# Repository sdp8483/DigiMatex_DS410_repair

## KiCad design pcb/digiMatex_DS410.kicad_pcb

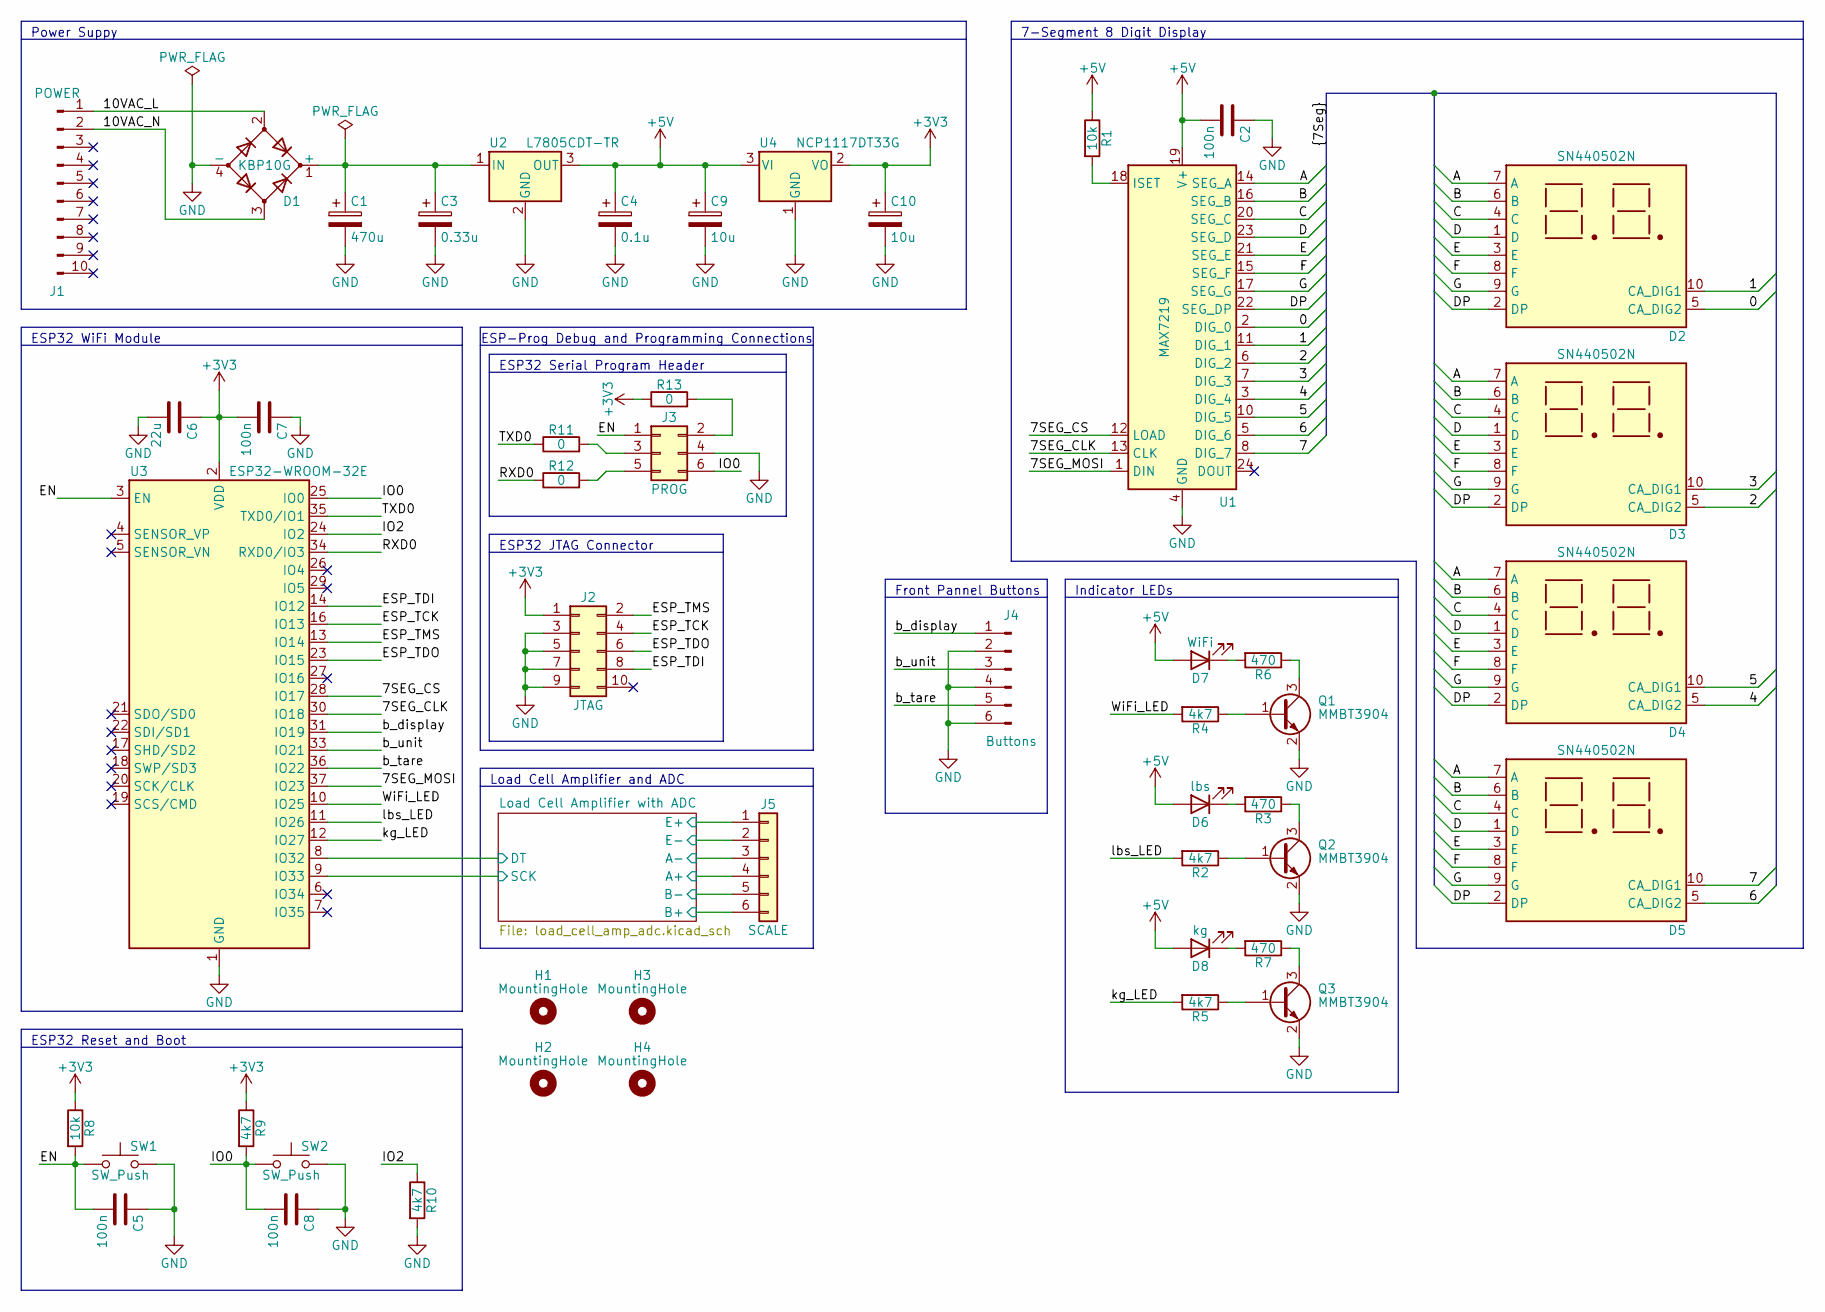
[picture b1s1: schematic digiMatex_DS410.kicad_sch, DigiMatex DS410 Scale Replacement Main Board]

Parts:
C1: 470u; CP_Radial_D10.0mm_P5.00mm
C2, C5, C7, C8: 100n; C_0603_1608Metric
C3: 0.33u; CP_Radial_D6.3mm_P2.50mm
C4: 0.1u; CP_Radial_D6.3mm_P2.50mm
C6: 22u; C_1206_3216Metric
C9, C10: 10u; CP_Radial_D6.3mm_P2.50mm
D1: KBP10G; Diode_Bridge_Vishay_KBPM
D2, D3, D4, D5: SN440502N
D6: lbs; LED_D5.0mm
D7: WiFi; LED_D5.0mm
D8: kg; LED_D5.0mm
H1, H2, H3, H4: MountingHole; MountingHole_4mm_Pad
J1: POWER; Molex_KK-254_AE-6410-10A_1x10_P2.54mm_Vertical
J2: JTAG; PinHeader_2x05_P2.54mm_Vertical
J3: PROG; PinHeader_2x03_P2.54mm_Vertical
J4: Buttons; Molex_KK-254_AE-6410-06A_1x06_P2.54mm_Vertical
J5: SCALE; TerminalBlock_Phoenix_MKDS-1,5-6_1x06_P5.00mm_Horizontal
Q1, Q2, Q3: MMBT3904; SOT-23
R1, R8: 10k; R_0603_1608Metric_Pad0.98x0.95mm_HandSolder
R2, R4, R5, R9, R10: 4k7; R_0603_1608Metric_Pad0.98x0.95mm_HandSolder
R3, R6, R7: 470; R_Axial_DIN0207_L6.3mm_D2.5mm_P10.16mm_Horizontal
R11, R12, R13: 0; R_0805_2012Metric_Pad1.20x1.40mm_HandSolder
SW1, SW2: SW_Push; SW_PUSH_6mm
U1: MAX7219; SOIC-24W_7.5x15.4mm_P1.27mm
U2: L7805CDT-TR; TO-252-2
U3: ESP32-WROOM-32E; ESP32-WROOM-32
U4: NCP1117DT33G; TO-252-2

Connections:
+3V3: C6.1, C7.2, C10.1, J2.1, R8.1, R9.1, R13.1, U3.2 (VDD), U4.2 (VO); also elsewhere on the board
+5V: C2.2, C4.1, C9.1, D6.2 (A), D7.2 (A), D8.2 (A), R1.1, U1.19 (V+), U2.3 (OUT), U4.3 (VI); also elsewhere on the board
/0: D2.5 (CA_DIG2), U1.2 (DIG_0)
/1: D2.10 (CA_DIG1), U1.11 (DIG_1)
/2: D3.5 (CA_DIG2), U1.6 (DIG_2)
/3: D3.10 (CA_DIG1), U1.7 (DIG_3)
/4: D4.5 (CA_DIG2), U1.3 (DIG_4)
/5: D4.10 (CA_DIG1), U1.10 (DIG_5)
/6: D5.5 (CA_DIG2), U1.5 (DIG_6)
/7: D5.10 (CA_DIG1), U1.8 (DIG_7)
/7SEG_CLK: U1.13 (CLK), U3.30 (IO18)
/7SEG_CS: U1.12 (LOAD), U3.28 (IO17)
/7SEG_MOSI: U1.1 (DIN), U3.37 (IO23)
/10VAC_L: D1.2, J1.1
/10VAC_N: D1.3, J1.2
/A: D2.7 (A), D3.7 (A), D4.7 (A), D5.7 (A), U1.14 (SEG_A)
/B: D2.6 (B), D3.6 (B), D4.6 (B), D5.6 (B), U1.16 (SEG_B)
/C: D2.4 (C), D3.4 (C), D4.4 (C), D5.4 (C), U1.20 (SEG_C)
/D: D2.1 (D), D3.1 (D), D4.1 (D), D5.1 (D), U1.23 (SEG_D)
/DP: D2.2 (DP), D3.2 (DP), D4.2 (DP), D5.2 (DP), U1.22 (SEG_DP)
/E: D2.3 (E), D3.3 (E), D4.3 (E), D5.3 (E), U1.21 (SEG_E)
/EN: C5.2, J3.1, R8.2, SW1.1, U3.3 (EN)
/ESP_TCK: J2.4, U3.16 (IO13)
/ESP_TDI: J2.8, U3.14 (IO12)
/ESP_TDO: J2.6, U3.23 (IO15)
/ESP_TMS: J2.2, U3.13 (IO14)
/F: D2.8 (F), D3.8 (F), D4.8 (F), D5.8 (F), U1.15 (SEG_F)
/G: D2.9 (G), D3.9 (G), D4.9 (G), D5.9 (G), U1.17 (SEG_G)
/IO0: C8.2, J3.6, R9.2, SW2.1, U3.25 (IO0)
/IO2: R10.1, U3.24 (IO2)
/Load Cell Amplifier with ADC/A+: J5.4; also elsewhere on the board
/Load Cell Amplifier with ADC/A-: J5.3; also elsewhere on the board
/Load Cell Amplifier with ADC/B+: J5.6; also elsewhere on the board
/Load Cell Amplifier with ADC/B-: J5.5; also elsewhere on the board
/Load Cell Amplifier with ADC/DT: U3.8 (IO32); also elsewhere on the board
/Load Cell Amplifier with ADC/E+: J5.1; also elsewhere on the board
/Load Cell Amplifier with ADC/SCK: U3.9 (IO33); also elsewhere on the board
/RXD0: R12.1, U3.34 (RXD0/IO3)
/TXD0: R11.1, U3.35 (TXD0/IO1)
/WiFi_LED: R4.2, U3.10 (IO25)
/b_display: J4.1, U3.31 (IO19)
/b_tare: J4.5, U3.36 (IO22)
/b_unit: J4.3, U3.33 (IO21)
/kg_LED: R5.2, U3.12 (IO27)
/lbs_LED: R2.2, U3.11 (IO26)
GND: C1.2, C2.1, C3.2, C4.2, C5.1, C6.2, C7.1, C8.1, C9.2, C10.2, D1.4 (-), J2.3, J2.5, J2.7, J2.9, J3.4, J4.2, J4.4, J4.6, Q1.2 (E), Q2.2 (E), Q3.2 (E), R10.2, SW1.2, SW2.2, U1.4 (GND), U1.9 (GND), U2.2 (GND), U3.1 (GND), U3.15 (GND), U3.38 (GND), U3.39 (GND), U4.1 (GND); also elsewhere on the board
GNDA: J5.2; also elsewhere on the board
unnamed: C1.1, C3.1, D1.1 (+), U2.1 (IN)
unnamed: D6.1 (K), R3.2
unnamed: D7.1 (K), R6.2
unnamed: D8.1 (K), R7.2
unnamed: J3.2, R13.2
unnamed: J3.3, R11.2
unnamed: J3.5, R12.2
unnamed: Q1.1 (B), R4.1
unnamed: Q1.3 (C), R6.1
unnamed: Q2.1 (B), R2.1
unnamed: Q2.3 (C), R3.1
unnamed: Q3.1 (B), R5.1
unnamed: Q3.3 (C), R7.1
unnamed: R1.2, U1.18 (ISET)

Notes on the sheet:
Front Pannel Buttons
ESP32 Reset and Boot
Power Suppy
7-Segment 8 Digit Display
Load Cell Amplifier and ADC
Indicator LEDs
ESP-Prog Debug and Programming Connections
ESP32 JTAG Connector
ESP32 Serial Program Header
ESP32 WiFi Module

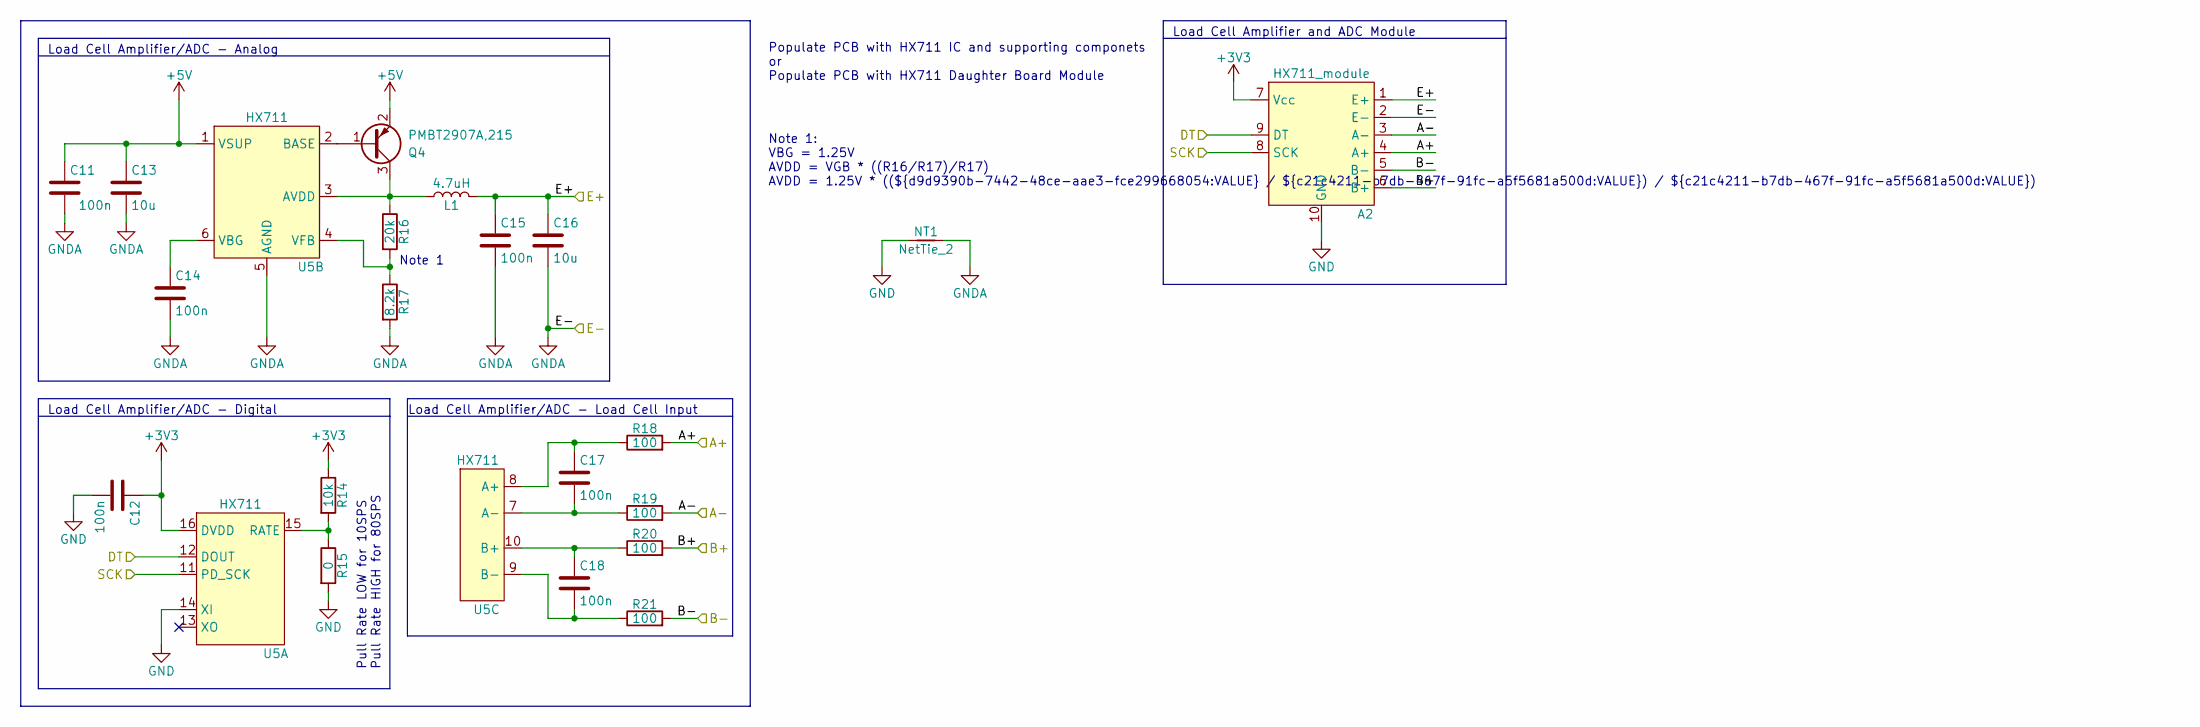
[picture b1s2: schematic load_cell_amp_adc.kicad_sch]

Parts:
A2: HX711_module
C11, C12, C14, C15, C17, C18: 100n; C_0603_1608Metric
C13, C16: 10u; C_0805_2012Metric_Pad1.18x1.45mm_HandSolder
L1: 4.7uH; L_0805_2012Metric_Pad1.05x1.20mm_HandSolder
NT1: NetTie_2; NetTie-2_SMD_Pad2.0mm
Q4: PMBT2907A,215; SOT-23
R14: 10k; R_0603_1608Metric_Pad0.98x0.95mm_HandSolder
R15: 0; R_0603_1608Metric_Pad0.98x0.95mm_HandSolder
R16: 20k; R_0805_2012Metric_Pad1.20x1.40mm_HandSolder
R17: 8.2k; R_0805_2012Metric_Pad1.20x1.40mm_HandSolder
R18, R19, R20, R21: 100; R_0603_1608Metric_Pad0.98x0.95mm_HandSolder
U5: HX711; SOP-16_3.9x9.9mm_P1.27mm

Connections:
+3V3: A2.7 (Vcc), C12.1, R14.1, U5.16 (DVDD); also elsewhere on the board
+5V: C11.1, C13.1, Q4.2 (E), U5.1 (VSUP); also elsewhere on the board
/Load Cell Amplifier with ADC/A+: A2.4 (A+), R18.2; also elsewhere on the board
/Load Cell Amplifier with ADC/A-: A2.3 (A-), R19.2; also elsewhere on the board
/Load Cell Amplifier with ADC/B+: A2.6 (B+), R20.2; also elsewhere on the board
/Load Cell Amplifier with ADC/B-: A2.5 (B-), R21.2; also elsewhere on the board
/Load Cell Amplifier with ADC/DT: A2.9 (DT), U5.12 (DOUT); also elsewhere on the board
/Load Cell Amplifier with ADC/E+: A2.1 (E+), C15.1, C16.1, L1.1; also elsewhere on the board
/Load Cell Amplifier with ADC/SCK: A2.8 (SCK), U5.11 (PD_SCK); also elsewhere on the board
GND: A2.10 (GND), C12.2, NT1.1, R15.2, U5.14 (XI); also elsewhere on the board
GNDA: A2.2 (E-), C11.2, C13.2, C14.2, C15.2, C16.2, NT1.2, R17.2, U5.5 (AGND); also elsewhere on the board
unnamed: C14.1, U5.6 (VBG)
unnamed: C17.1, R18.1, U5.8 (A+)
unnamed: C17.2, R19.1, U5.7 (A-)
unnamed: C18.1, R20.1, U5.10 (B+)
unnamed: C18.2, R21.1, U5.9 (B-)
unnamed: L1.2, Q4.3 (C), R16.1, U5.3 (AVDD)
unnamed: Q4.1 (B), U5.2 (BASE)
unnamed: R14.2, R15.1, U5.15 (RATE)
unnamed: R16.2, R17.1, U5.4 (VFB)

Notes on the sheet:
Note 1: VBG = 1.25V AVDD = VGB * ((R16/R17)/R17) AVDD = 1.25V * ((${d9d9390b-7442-48ce-aae3-fce299668054:VALUE} / ${c21c4211-b7db-467f-91fc-a5f5681a500d:VALUE}) / ${c21c4211-b7db-467f-91fc-a5f5681a500d:VALUE})
Pull Rate LOW for 10SPS Pull Rate HIGH for 80SPS
Populate PCB with HX711 IC and supporting componets or Populate PCB with HX711 Daughter Board Module
Load Cell Amplifier/ADC - Analog
Load Cell Amplifier/ADC - Load Cell Input
Load Cell Amplifier and ADC Module
Load Cell Amplifier/ADC - Digital
Note 1

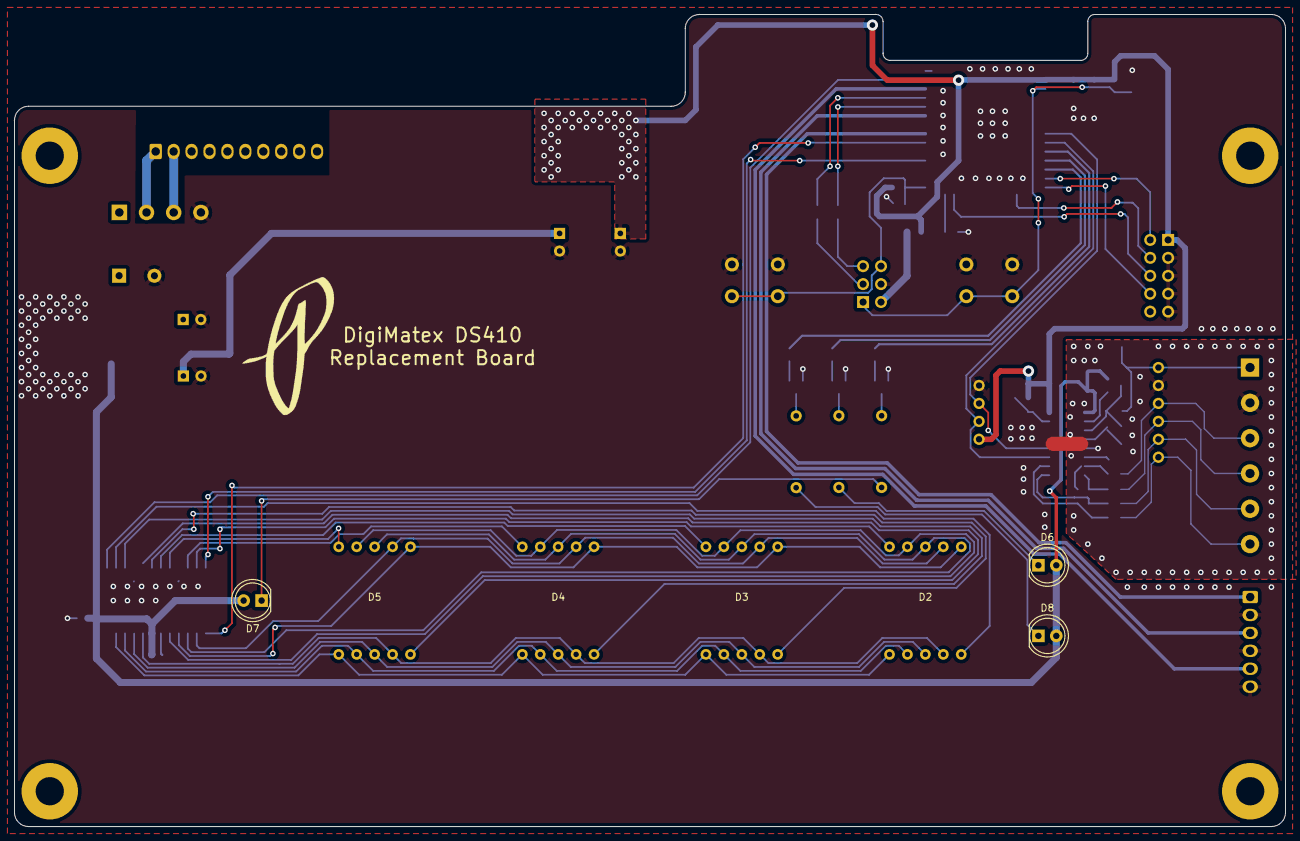
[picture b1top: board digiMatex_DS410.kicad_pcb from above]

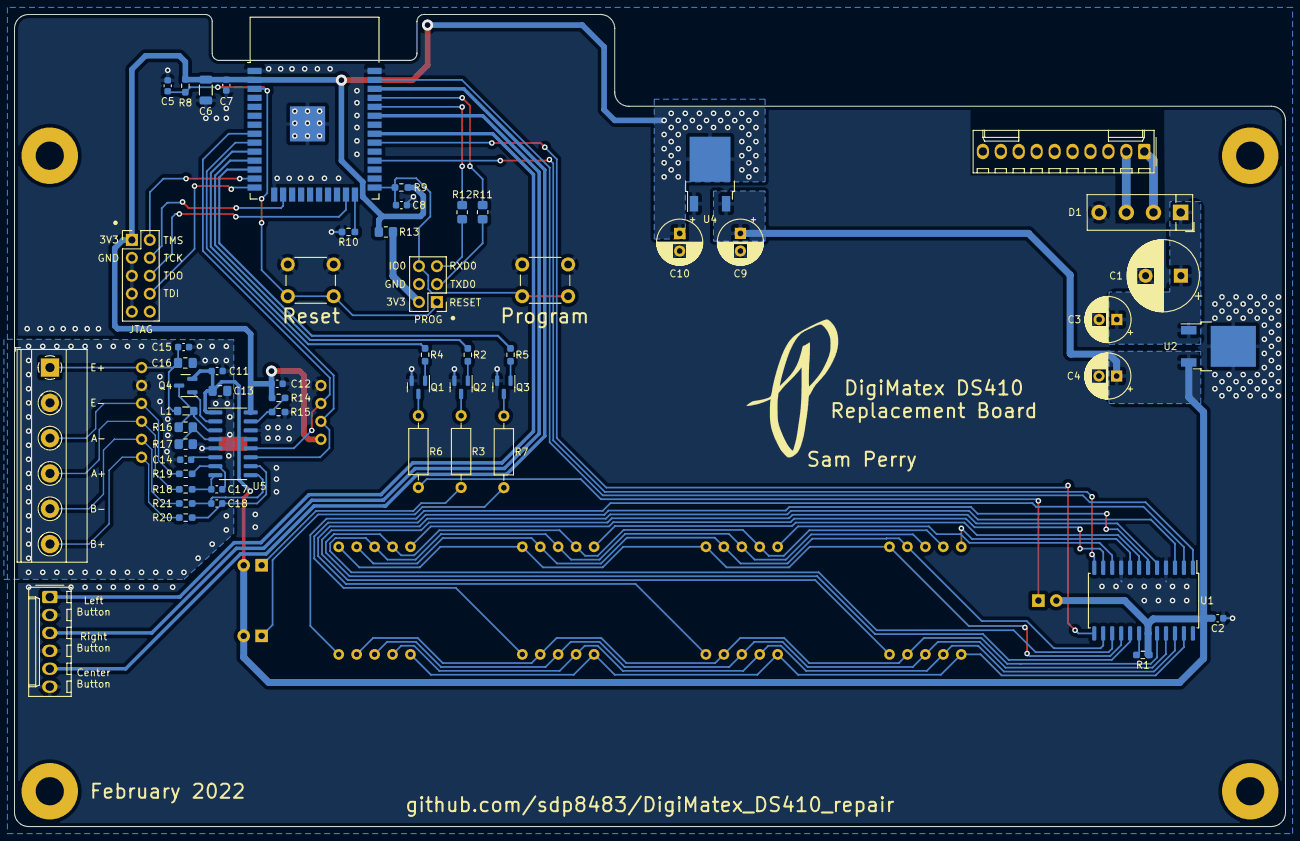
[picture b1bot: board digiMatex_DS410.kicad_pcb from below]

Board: 2 copper layers, 180.0 x 115.0 mm, 70 parts (58 on the bottom side), 70 nets.

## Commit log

2020-03-04 init empty defualt commit
2020-03-04 early code, need to unzip and setup repo for eclipse workspace
2020-03-11 move file
2020-03-11 generate init code
2020-03-11 add libs
2020-03-11 add previous code
2020-03-11 increase heap size to 0x400
2020-03-12 move user macros to user code pm area
2020-03-12 save calibartion data to eeprom
2020-03-12 tare displayed value
2020-03-12 increase buffer size to reduce overshoot
2022-01-25 remove old files
2022-01-25 ignore zip backups
2022-01-30 remove stm32 fw
2022-01-30 init fw
2022-01-30 init schematic
2022-01-30 add mounts, buttons, and LEDs
2022-01-30 start pcb layout
2022-02-04 replace mini-360 with 7805 regulator
2022-02-05 add bridge model
2022-02-05 add esp32 model
2022-02-06 update hx711 pins
2022-02-06 export pdf
2022-02-06 final pcb layout
2022-02-06 add hx711 datasheet
2022-02-06 export gerber
2022-02-07 generate gcode
2022-02-13 update gcode
2022-02-21 rev A schematic with more SMD
2022-02-25 ignore #auto_saved_files#
2022-02-25 start pcb layout rev A
2022-02-26 use resistor footprints
2022-02-26 rev A layout
2022-02-27 revA gerbers
2022-02-27 add HX711 IC to main board
2022-02-27 rev b layout
2022-02-27 rev b gerber
2022-03-26 generate revB ibom
2022-03-27 add load cell pinout
2022-03-28 start
2022-03-29 bare firmware
2022-03-29 implement wifi led
2022-03-29 adjustable decimal places
2022-03-29 misspelled "type" for dec input
2022-03-29 disable lastpass in ssid input
2022-03-29 start setting up window sampling
2022-04-07 implemented all major functions
2022-04-08 implement htmlmin
2022-04-08 htmlmin breaks js
2022-04-09 fix errors
2022-04-09 send non average value
2022-04-09 implement div by 0 protections
2022-04-09 fix unit button
